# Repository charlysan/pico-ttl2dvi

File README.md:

# pico-ttl2dvi

Firmware and hardware for the RP2350 that captures **digital TTL video** from retro PC graphics cards and outputs **DVI/HDMI**, live.

TTL signals go straight into the RP2350, are sampled by PIO, 
reconstructed into a framebuffer, and re-emitted as DVI by 
[PicoDVI](https://github.com/Wren6991/PicoDVI).

> **Disclaimer.** This is an experimental hobby project. The firmware and
> hardware designs are shared as they are, with no warranty of any kind. Wiring
> a graphics card to a microcontroller means connecting 5V signals to a 3.3V
> chip, and a mistake can damage your graphics card, PC, monitor, RP2350 board
> or anything else attached. Build and use it at your own risk. The author
> accepts no responsibility for any damage or loss that results.

## Table of contents

- [Supported sources](#supported-sources)
- [Wiring](#wiring)
  - [Direct (resistors only)](#direct-resistors-only)
  - [Buffered (74HCT541 + resistors) - recommended, through-hole](#buffered-74hct541--resistors---recommended-through-hole)
  - [Buffered (74LVC245A, no resistors) - best](#buffered-74lvc245a-no-resistors---best)
  - [Controls: buttons and IR remote (optional)](#controls-buttons-and-ir-remote-optional)
- [Adapter board](#adapter-board)
- [Quick start guide](#quick-start-guide)
- [How it works](#how-it-works)
- [Modules](#modules)
- [Console](#console)
- [Tuning a card](#tuning-a-card)
- [ttl2dviPanel](#ttl2dvipanel)
- [Build](#build)
- [Hardware](#hardware)
- [Screenshots](#screenshots)
- [Discussion](#discussion)
- [Acknowledgements](#acknowledgements)
- [Licence](#licence)

## Supported sources

| Source | Data lines | Dot clock | Output |
|---|---|---|---|
| MDA / Hercules (16 MHz clone crystal) | VIDEO + INTENSITY, 2-bit | 16.000 MHz | 4-level grey |
| CGA, 640-wide modes | RGBI, 4-bit | 14.323 MHz | 16 colours |
| Commodore 128 VDC, 80-column | RGBI, 4-bit | 16.000 MHz | 16 colours |
| EGA, 350-line modes | RGBrgb, 6-bit | 17.750 MHz | 64 colours |
| EGA, 200-line modes | RGBI, 4-bit | 14.161 MHz | 16 colours |

Supports text and graphics modes. CGA and EGA 200-line modes use the standard
CGA palette (including the IBM 5153 "brown" correction). EGA switches between
its 200 and 350-line modes live, following the card.

Colour sources are encoded as RGB222, which gives about 75% of full brightness.
Turn up the monitor's brightness to compensate.

## Wiring

DE-9 from the card, 330 Ω in series on every line, into the RP2350's 5 V-tolerant
inputs.

| Signal | DE-9 | GPIO |
|---|---|---|
| VIDEO (MDA) / Secondary BLUE (EGA) | 7 | 20 |
| INTENSITY / Secondary GREEN (EGA) | 6 | 21 |
| RED | 3 | 22 |
| GREEN | 4 | 23 |
| BLUE | 5 | 24 |
| Secondary RED (EGA) | 2 | 25 |
| VSYNC | 9 | 26 |
| HSYNC | 8 | 27 |
| GND | 1 | GND |

On EGA 350-line modes, pins 2, 6 and 7 carry secondary red, green and blue. In
200-line modes the card drives it like CGA: pin 6 is INTENSITY and pins 2 and 7
are unused. Pin 2 is never ground on EGA, so use only pin 1 for GND.

DVI output pins are per board (`cmake/boards.cmake` + `src/config/board.h`);
on the default **Waveshare RP2350-PiZero** they are GPIO 32-39.

### Direct (resistors only)

The minimal hookup. The 330 Ω limits current into the RP2350 pad's clamp diode
- that diode *is* the "5 V tolerance", and the resistor is what keeps it safe.

```
   graphics card (TTL, 5V)                     RP2350
   ───────────────────────                     ──────
   DE-9 7   VIDEO      ─────[ 330Ω ]────────►  GPIO 20
   DE-9 6   INTENSITY  ─────[ 330Ω ]────────►  GPIO 21
   DE-9 3   RED        ─────[ 330Ω ]────────►  GPIO 22
   DE-9 4   GREEN      ─────[ 330Ω ]────────►  GPIO 23
   DE-9 5   BLUE       ─────[ 330Ω ]────────►  GPIO 24
   DE-9 2   sRED       ─────[ 330Ω ]────────►  GPIO 25
   DE-9 9   VSYNC      ─────[ 330Ω ]────────►  GPIO 26
   DE-9 8   HSYNC      ─────[ 330Ω ]────────►  GPIO 27
   DE-9 1   GND        ────────────────────►   GND
```

With the pad clamping, each asserted line draws a few mA from the card. Power
the Pico first, then the PC; power the PC down first.

### Buffered (74HCT541 + resistors) - recommended, through-hole

A 5 V octal buffer between card and Pico. Its CMOS inputs draw ~0 current, so
the video card's drivers are not loaded, and a fault on the Pico side cannot
reach the card. The 330 Ω moves to the buffer's *outputs*, where 5 V logic meets
the 3.3 V pad.

```
                        ┌───────── 74HCT541 ────────┐
                        │ (5V, 100nF across 19-20p) |
   DE-9 7   VIDEO  ────►│ 2  A1              Y1  18 │──[330Ω]──►  GPIO 20
   DE-9 6   INTEN  ────►│ 3  A2              Y2  17 │──[330Ω]──►  GPIO 21
   DE-9 3   RED    ────►│ 4  A3              Y3  16 │──[330Ω]──►  GPIO 22
   DE-9 4   GREEN  ────►│ 5  A4              Y4  15 │──[330Ω]──►  GPIO 23
   DE-9 5   BLUE   ────►│ 6  A5              Y5  14 │──[330Ω]──►  GPIO 24
   DE-9 9   VSYNC  ────►│ 7  A6              Y6  13 │──[330Ω]──►  GPIO 26
   DE-9 8   HSYNC  ────►│ 8  A7              Y7  12 │──[330Ω]──►  GPIO 27
   DE-9 2   sRED   ────►│ 9  A8              Y8  11 │──[330Ω]──►  GPIO 25
                        │                           │
                 GND ──►│ 1  /OE1          /OE2  19 │◄── GND
                 GND ──►│ 10 GND            Vcc  20 │◄── +5V
                        └───────────────────────────┘

   DE-9 1   GND ─────────────── common ground ──────────────►  GND
```

Both `/OE` pins (1 and 19) must go to GND, and keep one common ground between
card, buffer and Pico.

Use the **HCT** part, not plain HC: its TTL-level input thresholds read a 5 V
TTL high reliably at 5 V Vcc.

### Buffered (74LVC245A, no resistors) - best

The same idea, but powered at **3.3 V**. LVC inputs accept 5.5 V regardless of
Vcc - 5 V tolerance is a designed-in property of the family, so the card connects 
straight in and the outputs are already 3.3 V logic.

```
                    ┌───────── 74LVC245A ─────────┐
                    │ (3.3V, 100nF across 10-20p) │
   DE-9 7  VIDEO ──►│ 2  A1                B1  18 │────►  GPIO 20
   DE-9 6  INTEN ──►│ 3  A2                B2  17 │────►  GPIO 21
   DE-9 3  RED   ──►│ 4  A3                B3  16 │────►  GPIO 22
   DE-9 4  GREEN ──►│ 5  A4                B4  15 │────►  GPIO 23
   DE-9 5  BLUE  ──►│ 6  A5                B5  14 │────►  GPIO 24
   DE-9 9  VSYNC ──►│ 7  A6                B6  13 │────►  GPIO 26
   DE-9 8  HSYNC ──►│ 8  A7                B7  12 │────►  GPIO 27
   DE-9 2  sRED  ──►│ 9  A8                B8  11 │────►  GPIO 25
                    │                             │
            +3V3 ──►│ 1  DIR                      │  DIR high = A→B
             GND ──►│ 19 /OE              Vcc  20 │◄── +3V3 (Pico 3V3 pin)
                    │ 10 GND                      │
                    └─────────────────────────────┘

   DE-9 1  GND ─────────────── common ground ──────────────►  GND
```

`DIR` high and `/OE` low enable the A→B direction; both must be tied, not left
floating. Power it from the Pico's **3V3** pin - the 5 V tolerance depends on
Vcc being 3.3 V.

Beyond dropping the resistors, this also removes the power-sequencing rule: LVC
supports partial power-down, so the card may be live while the Pico is off.

### Controls: buttons and IR remote (optional)

Three push buttons and an IR receiver drive a one-line on-screen menu, so the
box can be tuned without a computer. Both are optional.

| Function | GPIO | Header pin (Pi layout) |
|---|---|---|
| IR receiver output | 6 | 31 |
| Button PREV (previous / -1) | 7 | 26 |
| Button NEXT (next / +1) | 8 | 24 |
| Button ENTER (short: select, long: back) | 9 | 21 |

Hold **ENTER + PREV** for 2 s to reset, **ENTER + NEXT** for 2 s to reboot into
USB BOOTSEL (for a UF2). The screen counts down; let go to cancel.

```
   push buttons (each one to GND)              RP2350
   ──────────────────────────────              ──────
          ┌─── PREV ───┐
   GND ───┤            ├───────────────────►  GPIO 7
          └─── o  o ───┘
          ┌─── NEXT ───┐
   GND ───┤            ├───────────────────►  GPIO 8
          └─── o  o ───┘
          ┌── ENTER ───┐
   GND ───┤            ├───────────────────►  GPIO 9
          └─── o  o ───┘

   IR receiver (KY-022 / VS1838B)
   ──────────────────────────────
          ┌───────────┐
          │  KY-022   │
          │         S ├─────────────────────►  GPIO 6
          │       VCC ├──────┬──────────────◄  3V3
          │           │     ═╪═ 100nF 
          │         - ├──────┴───────────────  GND
          └───────────┘
```

- **No resistors.** The firmware enables the internal pull-ups, so a button
  reads low while pressed. Wire buttons to **GND**, not to 3V3 with
  pull-downs: RP2350 erratum E9 can latch an input with the internal pull-down
  at ~2 V.
- **Power the IR receiver from 3V3**, not 5 V: its output is pulled up to its
  own supply, so at 3V3 it connects straight to the GPIO.
- **Put a 100 nF capacitor across the receiver's VCC and GND**, right at the
  module. Without it, the switching noise from the video inputs reaches the
  receiver through its supply, and its LED flickers 
  (observed when switching to EGA 350-line (1 px stripes or checkerboards).
- The remote must speak **NEC**, which most cheap remotes do.

To use a remote, either:

- **on the box:** Menu → Remote → Learn, then follow the on-screen prompts
  with the push buttons. It asks for the navigation keys, then offers
  shortcuts from a list (OSD status/live/hide, scanlines, load slot 0-7); or
- **from a computer:** record its buttons with `tools/irlearn.py --learn
  ir.txt`, turn the map into a UF2 with `tools/irmap2uf2.py ir.txt`, and drop
  `irmap.uf2` on the BOOTSEL drive (or `picotool load -f irmap.uf2`). This
  route can put any console command on a key.

Firmware updates leave the map in place.

## Adapter board

An experimental through-hole board design (KiCad) is in [hardware/tht](./hardware/tht/). See the [hardware documentation](./hardware/README.md) for how to build one.
Rev A is untested; only the breadboard prototype has been verified.

## Quick start guide

You can check the Quick Start Guide documentation [here](./docs/quickstart.md)

## How it works

```
  TTL video ──> [capture] ──> rawbuf ──> [view] ──> framebuffer ──> [video] ──> DVI
                pio0/core0                core0                   pio1/core1
                   ^
                   |
                [sync] ──> [sigcheck] ──> [detect] ──> reboot into another source
             HSYNC/VSYNC   rate check    auto source
             measurement
```

**No CPU sits in any per-line timing path.** PIO waits on sync edges; 
the CPU only acts once per frame, during vertical blanking. Capture and
DVI are on separate PIOs and separate cores, so neither can stall the other.

Core 0 only does the per-frame work: it waits for the VSYNC edge, sizes the
sampling window from the sync measurement, arms the DMA and the sampler, and
when the frame ends reconstructs it with `view`. Per line, the PIO locks to each
HSYNC edge and DMA stores the samples, with no CPU involved.

The source (card descriptor) configures both sides at boot: capture gets the
data pins, dot clock and default `bp`/`phase`; video gets the DVI raster and
encoder.

Per frame:

1. **`sync`** measures the HSYNC period and pulse width with a PIO countdown.
2. **`capture`** sizes its sampling window from that measurement, then a single
   DMA transfer records one VSYNC-bounded frame of raw samples into `rawbuf`.
   Sampling is 1x or 2x, picked per source: 2x when the dot clock is not close
   enough to a whole number of system clocks, so reconstruction can pick the
   sample nearest each pixel's centre rather than its edge.
3. **`view`** reconstructs each line, maps sample values to grey levels or
   RGB222 colours, and writes the result into the framebuffer at the current
   position (`hpos`/`vpos`).
4. **`video`** on core 1 walks the framebuffer, repeats rows for vertical scale,
   adds the letterbox, TMDS-encodes each scanline and feeds the serialiser
   continuously.

**Signal check and auto source.** `sigcheck` checks the HSYNC/VSYNC rates
against known ranges. Once they are stable, `detect` picks the source from the
line rate, and from the measured dot clock when several sources share a line
rate. If it finds a different card, it reboots into that source.

## Modules

| Path | Role |
|---|---|
| `src/config` | Board pins and DVI pin config; the source-card descriptors (pins, dot clock, sysclk, defaults) |
| `src/capture` | PIO sampler + DMA into `rawbuf`; per-line reconstruction; signal check. `capture.pio`, `sync_period.pio` |
| `src/video` | Framebuffer, DVI raster tables, TMDS encoding on core 1, colour tables |
| `src/view` | Scan converter: joins capture and video, owns all display framing |
| `src/settings` | Persistent settings slots in the last flash sector |
| `src/console` | USB CDC command console |
| `apps/ttl2dvi` | The application: startup order + command table (`main.c`), command bodies (`commands.c`), source detection (`detect.c`), OSD messages (`osd.c`), buttons and menu (`buttons.c`, `menu.c`), IR remote and learning (`remote.c`, `learn.c`), auto tune (`tune.c`) |
| `src/ir` | NEC IR decoder on pio2 |
| `apps/dvi_test` | Standalone DVI test card, links libdvi only |
| `extern/dvi` | Vendored PicoDVI (`libdvi`) (fork from [mlorenzati](https://github.com/mlorenzati/PicoDVI)) |
| `tools` | `ttl2dviPanel.py` control panel, `grab.py` frame grabber, `autotune.py` dot clock and phase tuning, `irlearn.py` / `irmap2uf2.py` IR key maps |

Everything that differs between cards - data pins, dot clock, system clock,
framebuffer depth, TMDS encoder, DVI raster - is selected from the source
descriptor at boot. Switching card reboots into the new configuration.

## Console

Connect to the USB serial port (115200 baud, any terminal) and type `help`.

```
source [n]           select the card (reboots)
source auto on|off   automatic source detection (stored in flash)
mode [n]             DVI output raster (reboots)
status / state       signal and settings; state prints one line for tools
bp / phase           capture framing: sampling window, sub-pixel sampling instant
dotclock [MHz]       card dot clock, or default
hpos / vpos          display position
vscale [1..4]        vertical scale
scanlines on|off|switch  blank every other line (vscale >= 2)
mdalevels            MDA grey levels
slots                saved settings for this source
save / load / clear  settings slots in flash (8 per source)
default [n|off]      slot applied at boot
detect / measure     which source auto would pick / measure the dot clock
tune [apply]         measure the dot clock and pick the phase (auto tune)
osd ...              on-screen display; osd live toggles live measurements
ir on|off / ir map   print IR remote codes / list the loaded key map
reboot / bootsel     reboot / reboot into USB BOOTSEL (for a UF2)
capture / fastcap    dump a frame over USB (tools/grab.py, tools/autotune.py)
dvi_test             on-screen test pattern
```

Example:
```
screen /dev/tty.usbmodem1101 115200

ttl2dvi> source
  auto detection: on
  0  MDA16  2 data bits @ GP20, 720 px, 16.000 MHz dot, sysclk 256 MHz   <- current
  1  CGA    4 data bits @ GP21, 640 px, 14.322 MHz dot, sysclk 258 MHz
  2  C128   4 data bits @ GP21, 640 px, 16.000 MHz dot, sysclk 256 MHz
  3  EGA    6 data bits @ GP20, 640 px, 17.750 MHz dot, sysclk 266.4 MHz, both families
ttl2dvi> source 1
switching to CGA...
```

## Tuning a card

If a card's crystal differs from the defaults, the picture shimmers or shows
evenly spaced vertical bars. Put text or a test pattern on screen, then:

- **on the box:** Menu → Sampling → Auto tune. It measures the dot clock from
  pixel edges, picks the phase, shows the result, and offers Apply, Apply and
  save to a slot, or Cancel;
- **on the console:** `tune` prints the same result, `tune apply` applies it;
- **from a computer:** `tools/autotune.py` does the same from a `fastcap`
  dump, with an edge histogram and the best phases listed.

Auto tune and `tune` search from -25% to +33% of the current dot clock, so a
card on a different crystal is usually found without changing the source.
If the result isn't a whole fraction of the system clock it says "may
shimmer": it works, but a source built for that clock would be cleaner.
`autotune.py` searches ±5%; for it, set `dotclock` near the card's first.
`bp` (the left edge) is not tuned. Save the result in a slot.

## ttl2dviPanel

`tools/ttl2dviPanel.py` is a Tk GUI over the same console
(`pip install -r tools/requirements.txt`). It polls `state` once a second, so
the knobs follow changes made from the console.

## Build

Requires the Pico SDK (2.3+) and CMake:

```sh
mkdir build && cd build
cmake -DTTL_BOARD=pizero ..
make -j
```

Or you can use [Docker](https://github.com/lukstep/raspberry-pi-pico-docker-sdk):

```sh
 docker run -d -it --name pico-sdk \
 --mount type=bind,source=${PWD},target=/home/dev \
 lukstep/raspberry-pi-pico-sdk:v1.2.0
 ```

```sh
docker exec -it pico-sdk sh -c \
"cd /home/dev/build && cmake \
-DTTL_BOARD=pizero \
-DPICO_PLATFORM=rp2350-arm-s .. \
&& make -j\$(nproc)"
```

`TTL_BOARD` selects the hardware profile (`pizero` | `pico2_dvi`) and is the
single source of truth for the board. The output is `build/apps/ttl2dvi/ttl2dvi.uf2`.

Then just upload the .uf2 file to rp2350 (in BOOTSEL mode). For example:
```sh
cp build/apps/ttl2dvi/ttl2dvi.uf2 /Volumes/RP2350
```

## Hardware

Tested on a [Waveshare RP2350-PiZero](https://www.waveshare.com/wiki/RP2350-PiZero) (RP2350B, 48 GPIO, 520 KB SRAM).

## Screenshots

Check [Wiki](https://github.com/charlysan/pico-ttl2dvi/wiki/Pico-TTL2DVI-Intro) for some screenshots.

## Discussion

- [VCFed](https://forum.vcfed.org/index.php?threads/pico-ttl2dvi-convert-ttl-video-to-hdmi.1258490/)

## Acknowledgements

Inspired by [mlorenzati/pico-rgb2hdmi](https://github.com/mlorenzati/pico-rgb2hdmi), which
converts analog RGB to HDMI on an RP2040. 

DVI output is [PicoDVI](https://github.com/Wren6991/PicoDVI) by Luke Wren.

## Licence

MIT.

`extern/dvi` is vendored PicoDVI and keeps its own licence - see
`extern/dvi/LICENSE`.

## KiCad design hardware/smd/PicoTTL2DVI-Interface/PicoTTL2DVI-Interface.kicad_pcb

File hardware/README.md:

# Hardware

Through-hole adapter board for the [Waveshare RP2350-PiZero](https://www.waveshare.com/wiki/RP2350-PiZero).
It takes the graphics card's TTL video on a DE-9 (or an IDC10 header), buffers it,
and feeds it to the RP2350. The HDMI output is the Waveshare's own mini HDMI.

> **Disclaimer.** Experimental hobby hardware, shared as it is, with no
> warranty. See the [main README](../README.md).

> **Not tested yet.** The rev A board has not been built (yet). The circuit was
> tested on a breadboard prototype (74HCT541 + 330 Ω), not on this PCB.

## Files

Everything for a revision is under `tht/rev<X>/`. For rev A:

| File | What |
|---|---|
| [`gerbers/ttl2dvi_tht_revA.zip`](./tht/revA/gerbers/ttl2dvi_tht_revA.zip) | Gerbers + drill files, ready to upload |
| [`BOM.txt`](./tht/revA/BOM.txt) | Bill of materials, with an "optional" column |
| [`schematic/schematic_tht_reva.pdf`](./tht/revA/schematic/schematic_tht_reva.pdf) | Schematic |
| `ttl2dvi_tht.kicad_*` | KiCad 10 project |

## Ordering the PCB

Upload the gerber `.zip` file as is to your PCB manufacturer (I've used JLCPCB constraints).
`THT` means that every part is through hole, so no assembly service is needed.

## HCT or LVC

U1 (buffer) and U2 (Schmitt) are socketed, and the board takes either logic
family. Pick one family for both chips.

| Build | U1 | U2 | Supply | Notes |
|---|---|---|---|---|
| **HCT** | 74HCT541 | 74HCT14 | 5 V | Keeps the power-sequencing rule (below). |
| **LVC** | 74LVC245A | 74LVC14A | 3.3 V | No power-sequencing rule. |

Both should work. However, I have only tested with HCT. LVC is the better choice if you can
get it though.

**HCT only: power the Pico first, then the PC. Turn the PC off first, then the
Pico.** With LVC the card may be live while the Pico is off.

R1-R8 (330 Ω) are fitted in both builds.

## Jumpers

All four are 1x3 headers. So, you can use a shunt or just solder a jumper.

| Jumper | Sets | 1-2 | 2-3 |
|---|---|---|---|
| JP1 | buffer supply | 3V3 (**LVC**) | 5V (**HCT**) |
| JP2 | U1 pin 1 | DIR, '245 (**LVC**) | /OE1, '541 (**HCT**) |
| JP3 | HSYNC source | U1 buffer | U2 Schmitt |
| JP4 | VSYNC source | U1 buffer | U2 Schmitt |

- JP1 and JP2 always go together: both on LVC, or both on HCT.
- **No U2 fitted: JP3 and JP4 on 1-2.** On 2-3 the syncs come from an empty
  socket and nothing is captured.

## What to populate

You do not need to fit everything. The minimum is:

- J1 (2x20 female header) and the Waveshare module
- J2 (DE-9) **or** J3 (IDC10)
- U1 + socket, C1, C2
- R1-R8
- JP1-JP4 + shunts

The rest is optional. Check the "optional" column in [`BOM.txt`](./tht/revA/BOM.txt).

| Part | What for |
|---|---|
| J3 | Alternative input: a DE9-to-IDC10 cable (IDC pin n = DE-9 pin n). **Use one input only**, never J2 and J3 at once |
| U2 + socket | Schmitt trigger on HSYNC/VSYNC. Not needed so far; added for experimentation when HSYNC is distorted / degraded. |
| SW1-SW3 | PREV / NEXT / ENTER buttons for the on-screen menu  (OSD)|
| U3, R9, C4 | IR receiver for a remote. R9 and C4 are required when U3 is fitted |
| D1, R10 | IR activity LED, for debugging |
| J4 | Logic analyser header (GPIO 20-27 + GND) |
| J5, R11, R12 | Serial console pins. R11/R12 sit under the module. |
| J6, D2 | External 5 V input |

## Mounting the Waveshare

The module plugs in **face down**: component side towards the adapter board,
with its USB-C and mini HDMI at the board edge. Its BOOT and RUN buttons are
not reachable that way. Use `picotool reboot -f -u`, the `bootsel` console
command, or hold **ENTER + NEXT** for 2 s to get into BOOTSEL.

## Power

Power the board from **either** the Waveshare's USB-C **or** J6 (5V IN).

> **NEVER connect J6 and a USB-C cable at the same time.** The 5 V pins on
> the header are the Waveshare's USB VBUS. D2 stops USB from feeding the
> external supply, but not the other way round!

Never feed anything into a 3V3 pin.

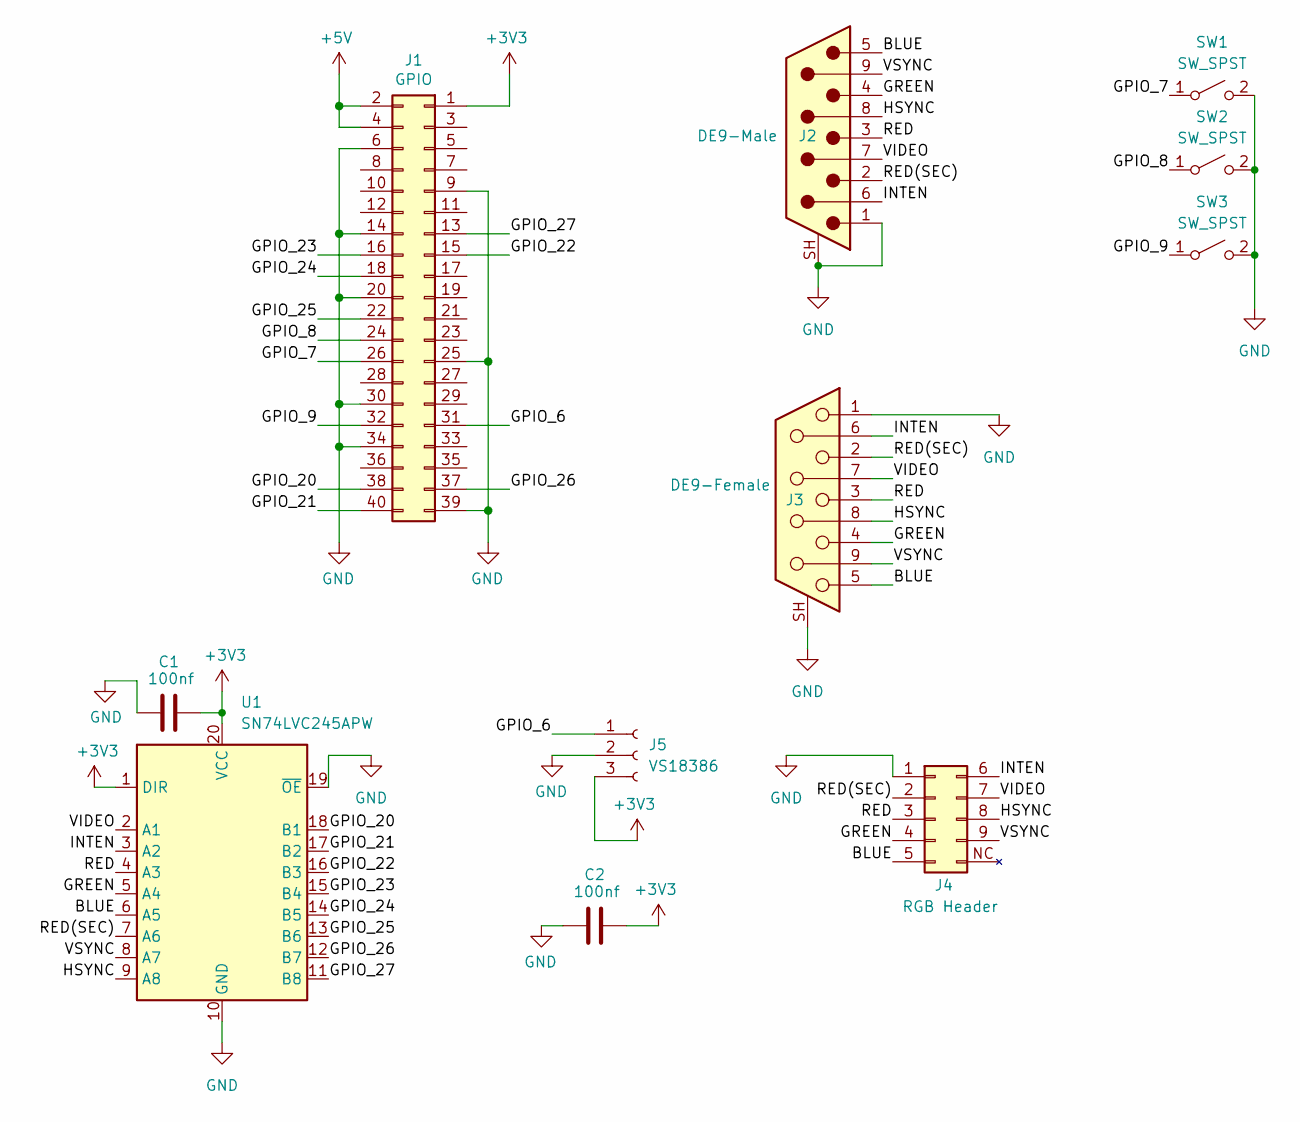
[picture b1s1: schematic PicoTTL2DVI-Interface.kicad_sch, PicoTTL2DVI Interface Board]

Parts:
C1, C2: 100nf; C_0805_2012Metric_Pad1.18x1.45mm_HandSolder
J1: GPIO; PinSocket_2x20_P2.54mm_Vertical
J2: DE9-Male; DSUB-9_Pins_EdgeMount_P2.77mm
J3: DE9-Female; DSUB-9_Socket_EdgeMount_P2.77mm
J4: RGB Header; PinHeader_2x05_P2.54mm_Vertical
J5: VS18386; PinHeader_1x03_P2.54mm_Vertical
SW1, SW2, SW3: SW_SPST; SW_PUSH_6mm
U1: SN74LVC245APW; TSSOP-20_4.4x6.5mm_P0.65mm

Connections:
+3V3: C1.2, C2.2, J1.1, J5.3, U1.1 (DIR), U1.20 (VCC)
+5V: J1.2, J1.4
/BLUE: J2.5, J3.5, J4.5, U1.6 (A5)
/GPIO_6: J1.31, J5.1
/GPIO_7: J1.26, SW1.1 (A)
/GPIO_8: J1.24, SW2.1 (A)
/GPIO_9: J1.32, SW3.1 (A)
/GPIO_20: J1.38, U1.18 (B1)
/GPIO_21: J1.40, U1.17 (B2)
/GPIO_22: J1.15, U1.16 (B3)
/GPIO_23: J1.16, U1.15 (B4)
/GPIO_24: J1.18, U1.14 (B5)
/GPIO_25: J1.22, U1.13 (B6)
/GPIO_26: J1.37, U1.12 (B7)
/GPIO_27: J1.13, U1.11 (B8)
/GREEN: J2.4, J3.4, J4.4, U1.5 (A4)
/HSYNC: J2.8, J3.8, J4.8, U1.9 (A8)
/INTEN: J2.6, J3.6, J4.6, U1.3 (A2)
/RED: J2.3, J3.3, J4.3, U1.4 (A3)
/RED(SEC): J2.2, J3.2, J4.2, U1.7 (A6)
/VIDEO: J2.7, J3.7, J4.7, U1.2 (A1)
/VSYNC: J2.9, J3.9, J4.9, U1.8 (A7)
GND: C1.1, C2.1, J1.6, J1.9, J1.14, J1.20, J1.25, J1.30, J1.34, J1.39, J2.1, J2.SH (PAD), J3.1, J3.SH (PAD), J4.1, J5.2, SW1.2 (B), SW2.2 (B), SW3.2 (B), U1.10 (GND), U1.19 (~OE)

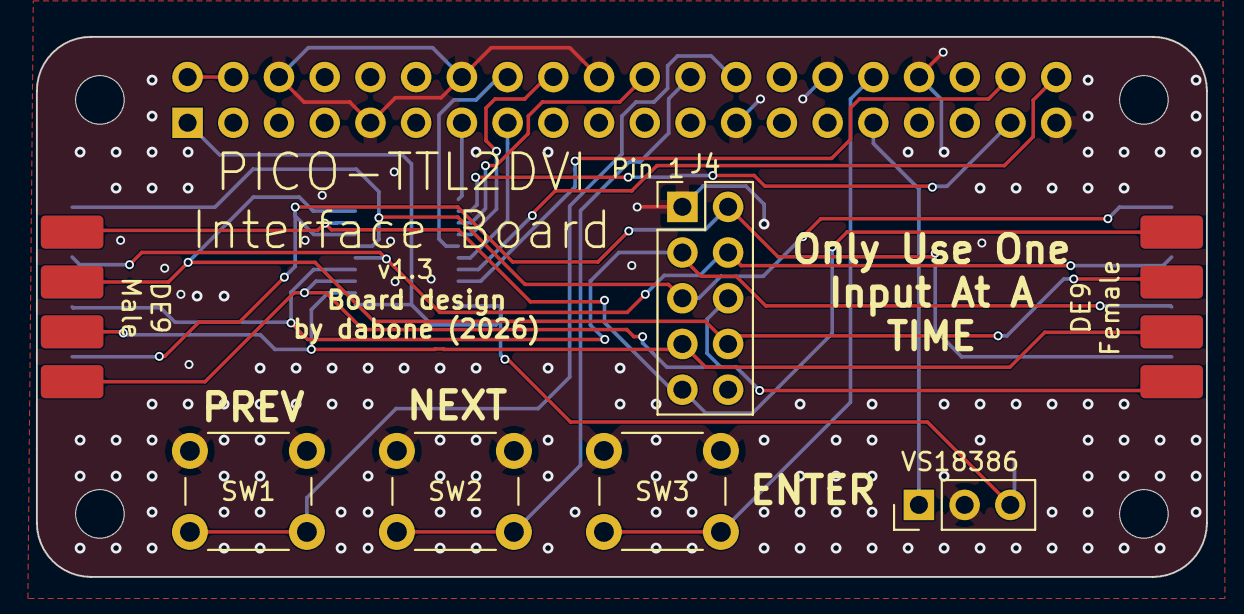
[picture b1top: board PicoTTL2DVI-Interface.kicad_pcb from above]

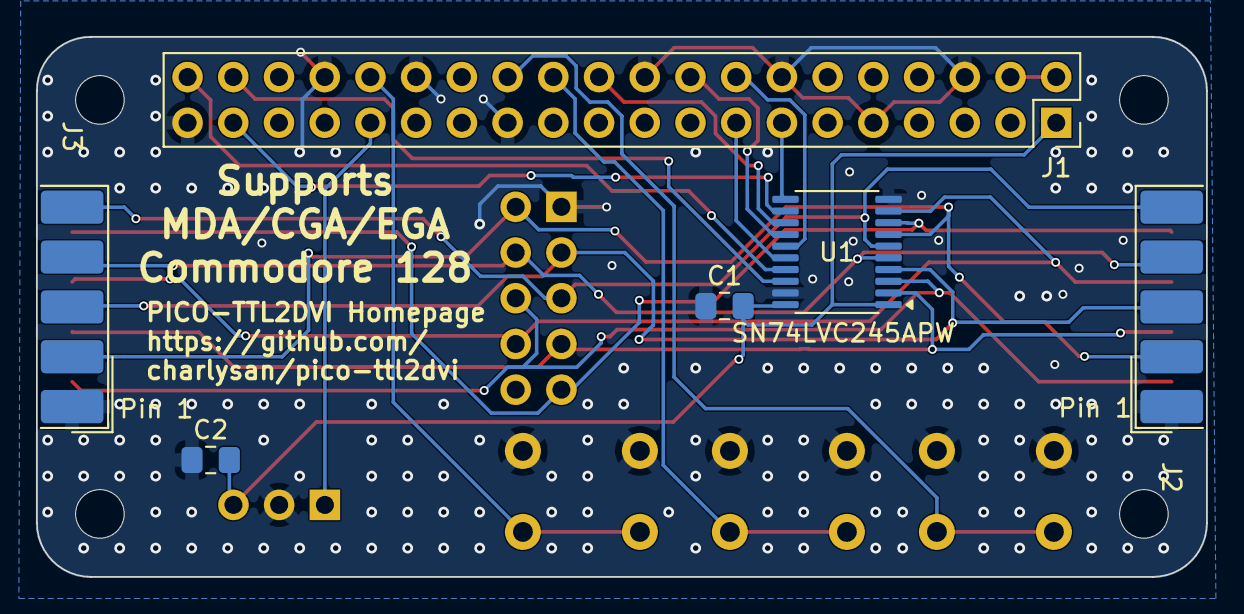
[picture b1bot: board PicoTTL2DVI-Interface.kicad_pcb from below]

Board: 2 copper layers, 65.0 x 30.0 mm, 15 parts (6 on the bottom side), 23 nets.

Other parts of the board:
MH1, MH2, MH3, MH4: MountingHole_2.7mm_M2.5

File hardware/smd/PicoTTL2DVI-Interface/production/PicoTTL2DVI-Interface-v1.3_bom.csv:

Designator,Footprint,Quantity,Value,LCSC Part #
"C1, C2",0805,2,100nf,
J1,PinSocket_2x20_P2.54mm_Vertical,1,GPIO,
J2,DSUB-9_Pins_EdgeMount_P2.77mm,1,DE9-Male,
J3,DSUB-9_Socket_EdgeMount_P2.77mm,1,DE9-Female,
J4,PinHeader_2x05_P2.54mm_Vertical,1,RGB Header,
J5,PinHeader_1x03_P2.54mm_Vertical,1,VS18386,
"SW1, SW2, SW3",SW_PUSH_6mm,3,SW_SPST,
U1,TSSOP-20_4.4x6.5mm_P0.65mm,1,SN74LVC245APW,

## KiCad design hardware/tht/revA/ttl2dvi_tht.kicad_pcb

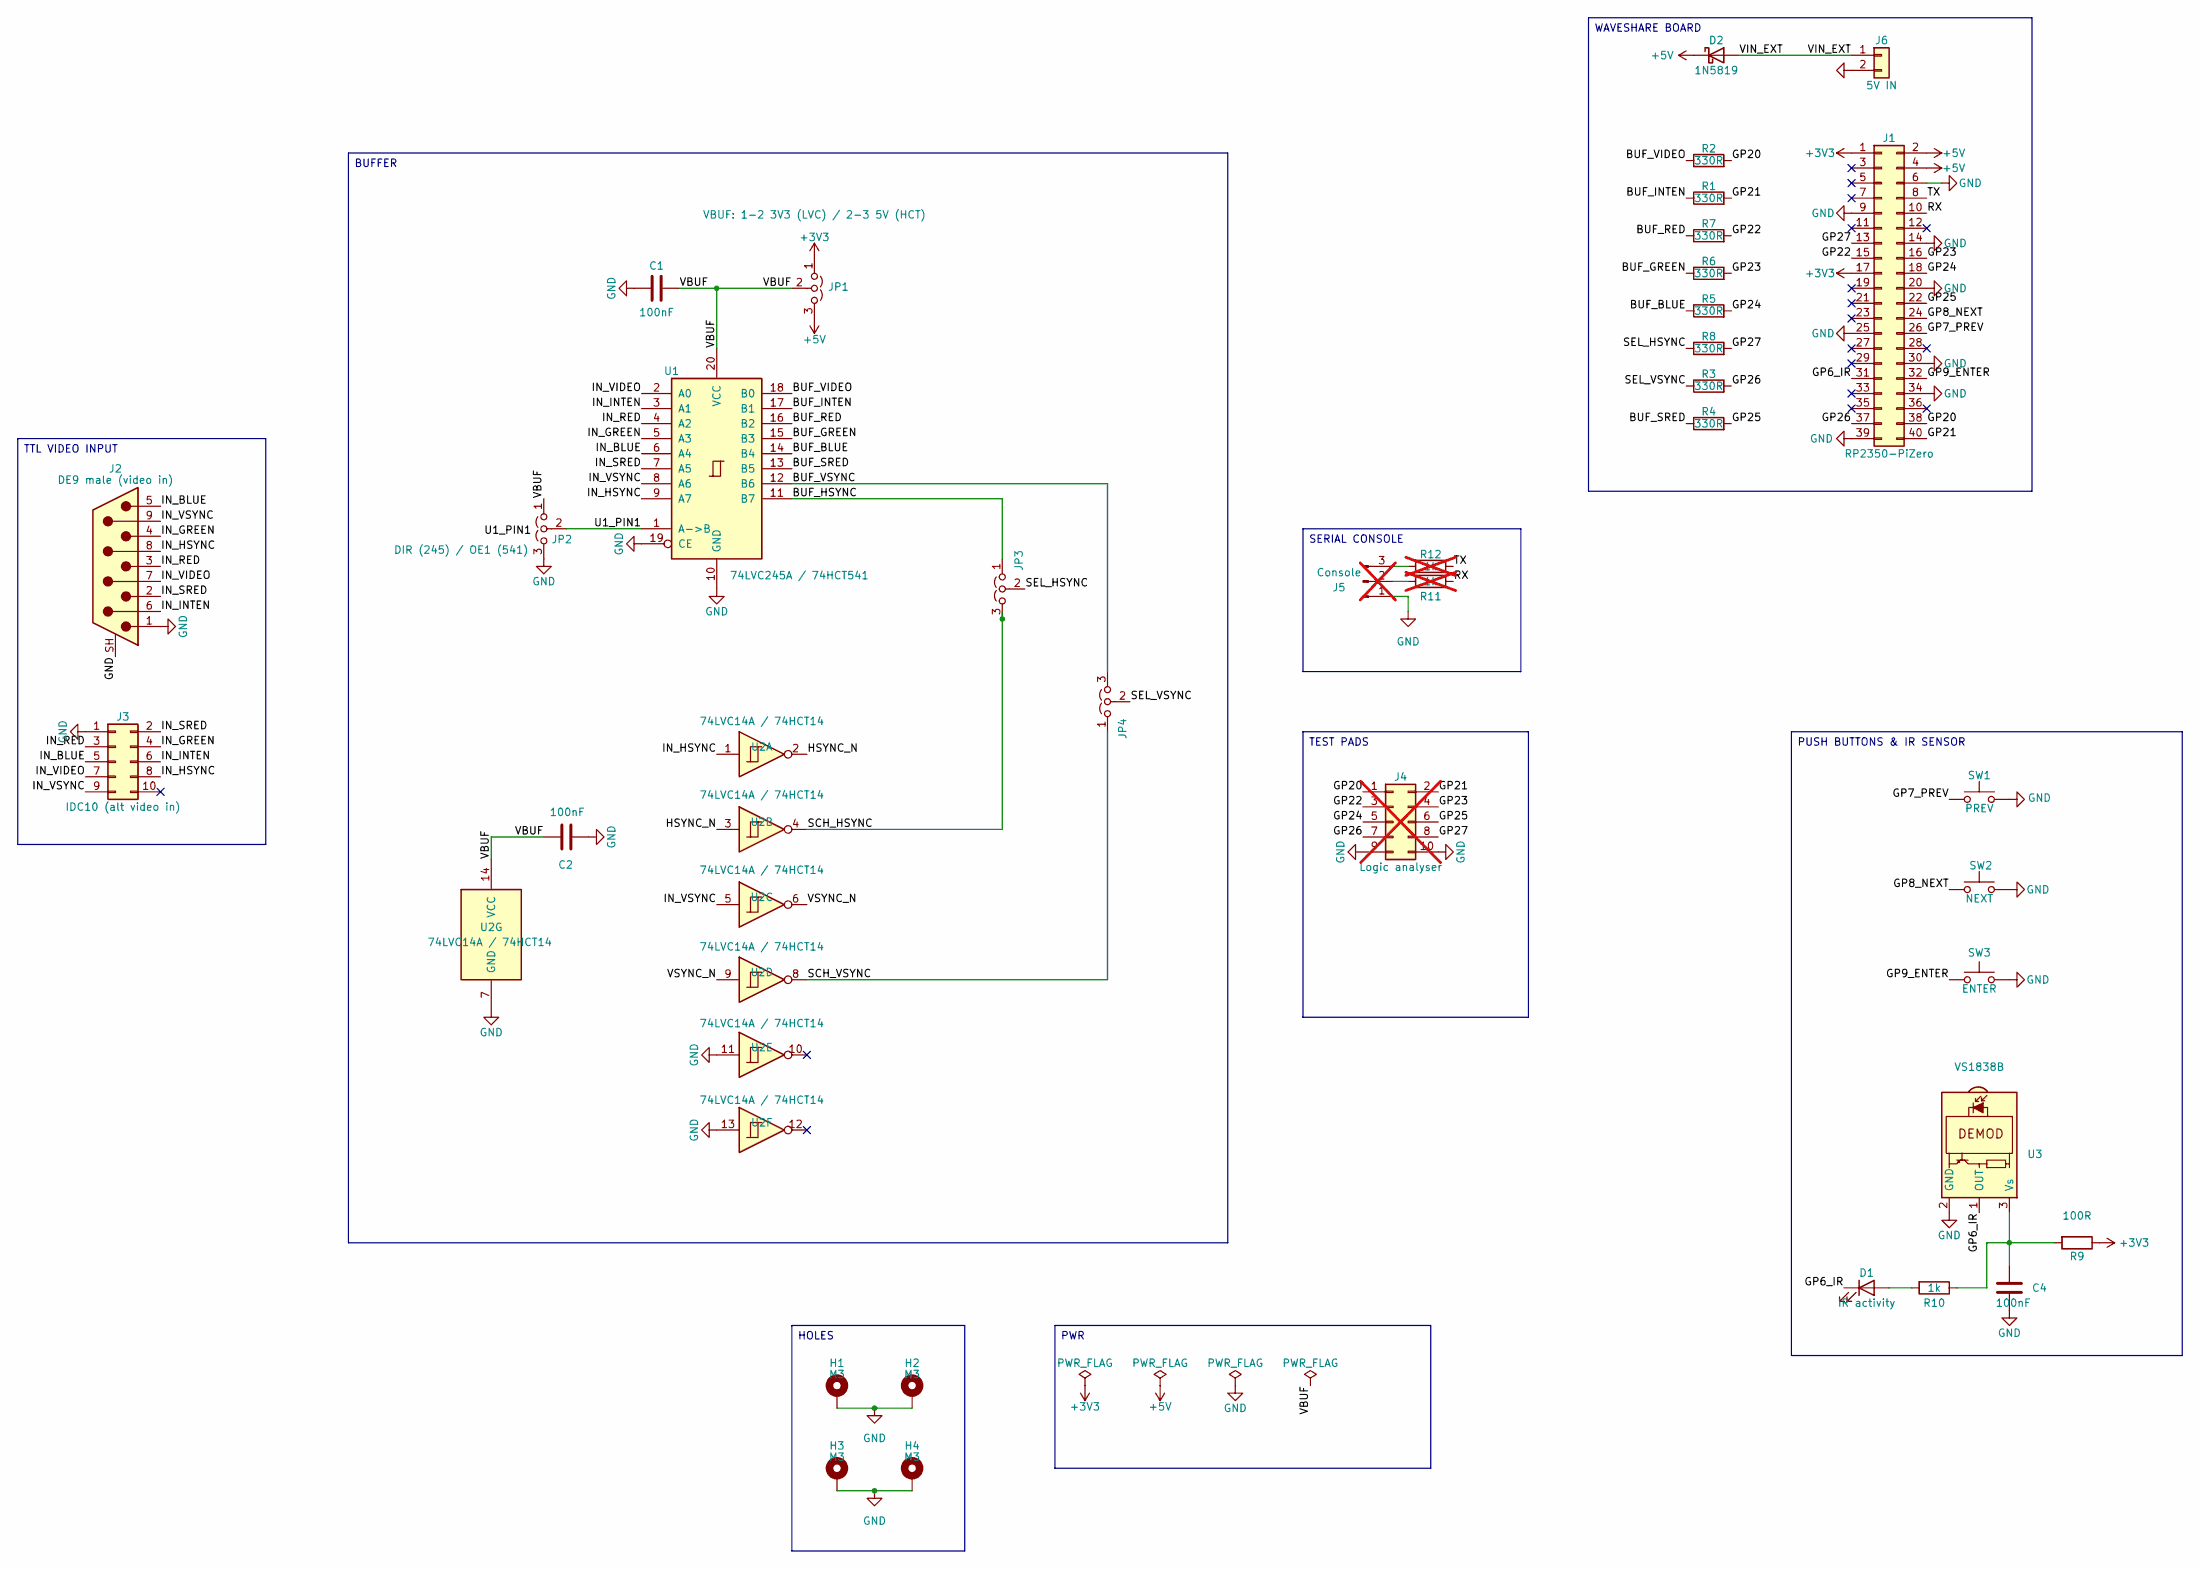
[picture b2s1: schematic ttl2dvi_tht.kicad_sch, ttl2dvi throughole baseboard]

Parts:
C1, C2, C4: 100nF; C_Disc_D5.0mm_W2.5mm_P5.00mm
D1: IR activity; LED_D3.0mm
D2: 1N5819; D_DO-41_SOD81_P10.16mm_Horizontal
H1, H2, H3, H4: M3; MountingHole_3.2mm_M3_Pad_Via
J1: RP2350-PiZero; Raspberry_Pi_Zero_Socketed_THT_FaceDown_MountingHoles
J2: DE9 male (video in); DSUB-9_Pins_Horizontal_P2.77x2.84mm_EdgePinOffset7.70mm_Hou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
J3: IDC10 (alt video in); IDC-Header_2x05_P2.54mm_Vertical
J4: Logic analyser; PinHeader_2x05_P2.54mm_Vertical; not fitted
J5: Console; PinHeader_1x03_P2.54mm_Vertical; not fitted
J6: 5V IN; JST_XH_B2B-XH-A_1x02_P2.50mm_Vertical
JP1: VBUF: 1-2 3V3 (LVC) / 2-3 5V (HCT); PinHeader_1x03_P2.54mm_Vertical
JP2: DIR (245) / OE1 (541); PinHeader_1x03_P2.54mm_Vertical
JP3: HSYNC: 1-2 BUF / 2-3 SCH; PinHeader_1x03_P2.54mm_Vertical
JP4: VSYNC: 1-2 BUF / 2-3 SCH; PinHeader_1x03_P2.54mm_Vertical
R1, R2, R3, R4, R5, R6, R7, R8: 330R; R_Axial_DIN0207_L6.3mm_D2.5mm_P7.62mm_Horizontal
R9: 100R; R_Axial_DIN0207_L6.3mm_D2.5mm_P7.62mm_Horizontal
R10: 1k; R_Axial_DIN0207_L6.3mm_D2.5mm_P7.62mm_Horizontal
R11, R12: 1k; R_Axial_DIN0207_L6.3mm_D2.5mm_P7.62mm_Horizontal; not fitted
SW1: PREV; SW_PUSH_6mm
SW2: NEXT; SW_PUSH_6mm
SW3: ENTER; SW_PUSH_6mm
U1: 74LVC245A / 74HCT541; DIP-20_W7.62mm_Socket
U2: 74LVC14A / 74HCT14; DIP-14_W7.62mm_Socket
U3: VS1838B; Vishay_MOLD-3Pin

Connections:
+3V3: J1.1, J1.17, JP1.1 (A), R9.1
+5V: D2.1 (K), J1.2, J1.4, JP1.3 (B)
/BUF_BLUE: R5.1, U1.14 (B4)
/BUF_GREEN: R6.1, U1.15 (B3)
/BUF_HSYNC: JP3.1 (A), U1.11 (B7)
/BUF_INTEN: R1.1, U1.17 (B1)
/BUF_RED: R7.1, U1.16 (B2)
/BUF_SRED: R4.1, U1.13 (B5)
/BUF_VIDEO: R2.1, U1.18 (B0)
/BUF_VSYNC: JP4.3 (B), U1.12 (B6)
/GP6_IR: D1.1 (K), J1.31, U3.1 (OUT)
/GP7_PREV: J1.26, SW1.1
/GP8_NEXT: J1.24, SW2.1
/GP9_ENTER: J1.32, SW3.1
/GP20: J1.38, J4.1, R2.2
/GP21: J1.40, J4.2, R1.2
/GP22: J1.15, J4.3, R7.2
/GP23: J1.16, J4.4, R6.2
/GP24: J1.18, J4.5, R5.2
/GP25: J1.22, J4.6, R4.2
/GP26: J1.37, J4.7, R3.2
/GP27: J1.13, J4.8, R8.2
/HSYNC_N: U2.2, U2.3
/IN_BLUE: J2.5, J3.5, U1.6 (A4)
/IN_GREEN: J2.4, J3.4, U1.5 (A3)
/IN_HSYNC: J2.8, J3.8, U1.9 (A7), U2.1
/IN_INTEN: J2.6, J3.6, U1.3 (A1)
/IN_RED: J2.3, J3.3, U1.4 (A2)
/IN_SRED: J2.2, J3.2, U1.7 (A5)
/IN_VIDEO: J2.7, J3.7, U1.2 (A0)
/IN_VSYNC: J2.9, J3.9, U1.8 (A6), U2.5
/RX: J1.10, R11.1
/SCH_HSYNC: JP3.3 (B), U2.4
/SCH_VSYNC: JP4.1 (A), U2.8
/SEL_HSYNC: JP3.2 (C), R8.1
/SEL_VSYNC: JP4.2 (C), R3.1
/TX: J1.8, R12.1
/U1_PIN1: JP2.2 (C), U1.1 (A->B)
/VBUF: C1.2, C2.1, JP1.2 (C), JP2.1 (A), U1.20 (VCC), U2.14 (VCC)
/VIN_EXT: D2.2 (A), J6.1
/VSYNC_N: U2.6, U2.9
GND: C1.1, C2.2, C4.2, H1.1 (1_1), H2.1 (1_1), H3.1 (1_1), H4.1 (1_1), J1.6, J1.9, J1.14, J1.20, J1.25, J1.30, J1.34, J1.39, J2.1, J2.SH (PAD), J3.1, J4.9, J4.10, J5.1, J6.2, JP2.3 (B), SW1.2, SW2.2, SW3.2, U1.10 (GND), U1.19 (CE), U2.7 (GND), U2.11, U2.13, U3.2 (GND)
unnamed: D1.2 (A), R10.2
unnamed: J5.2, R11.2
unnamed: J5.3, R12.2
unnamed: C4.1, R9.2, R10.1, U3.3 (Vs)

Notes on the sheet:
WAVESHARE BOARD
PUSH BUTTONS & IR SENSOR
TEST PADS
BUFFER
SERIAL CONSOLE
TTL VIDEO INPUT
HOLES
PWR

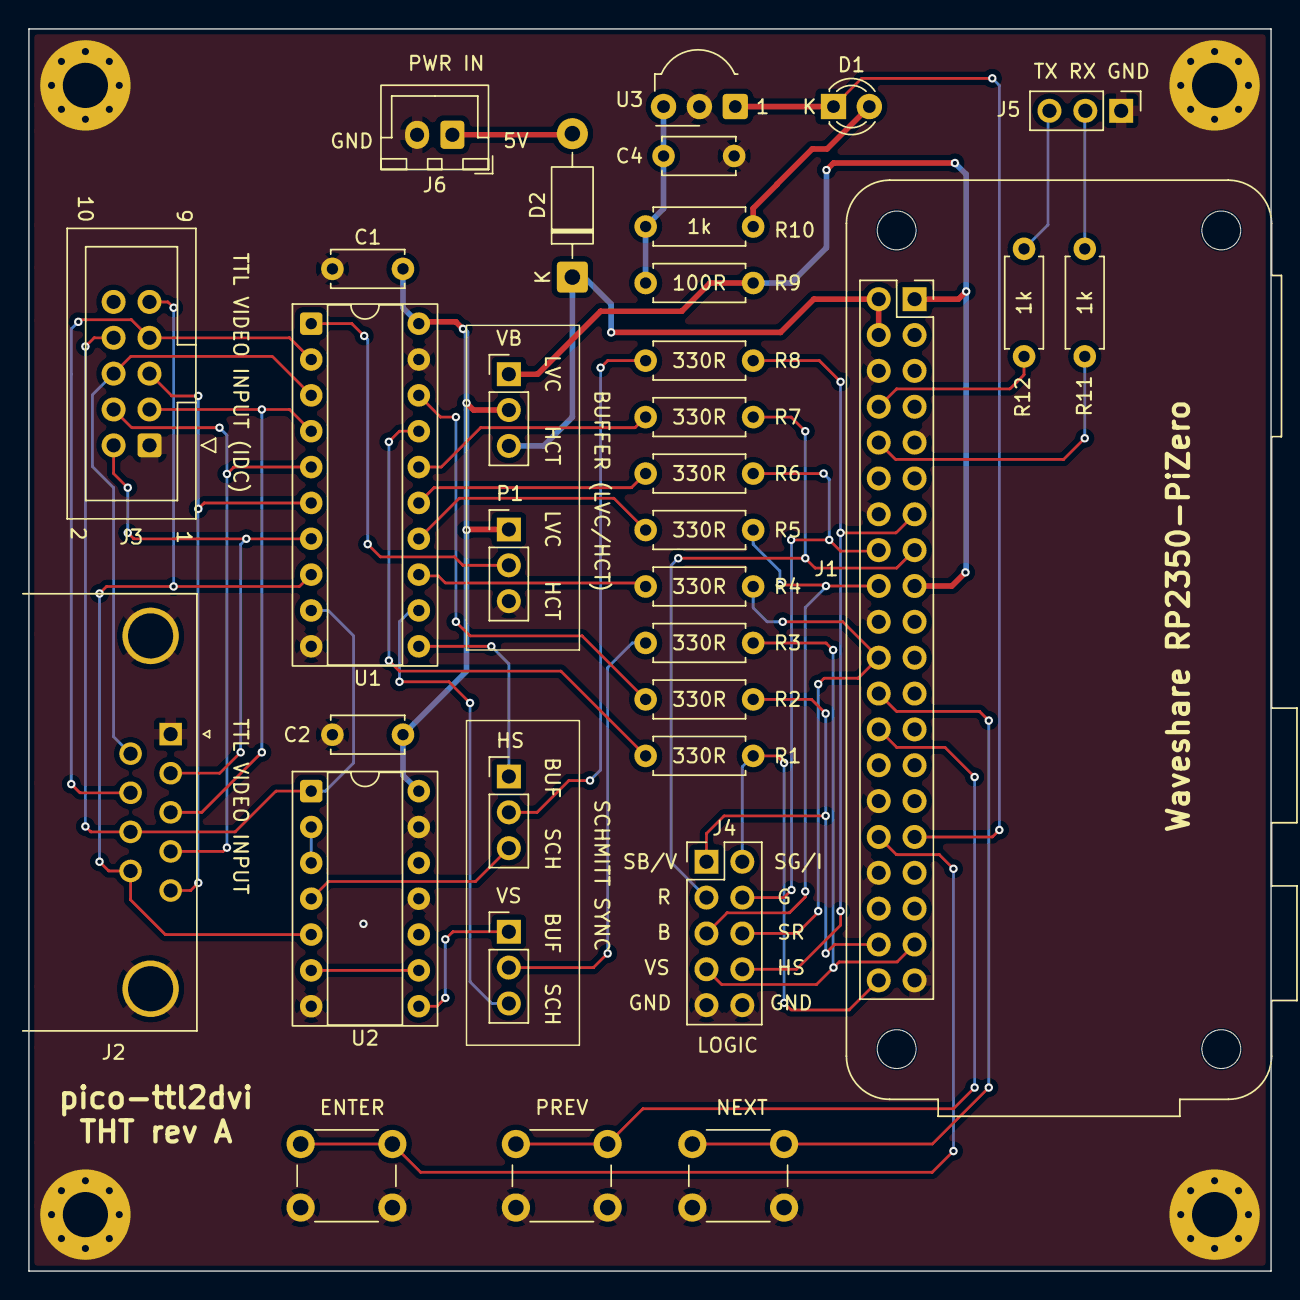
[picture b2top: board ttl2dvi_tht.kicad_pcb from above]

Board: 2 copper layers, 88.0 x 88.0 mm, 37 parts (0 on the bottom side), 46 nets.

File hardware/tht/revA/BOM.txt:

ttl2dvi THT adapter board - bill of materials (rev A)

Ref        Qty  Value / part                   Package                  Optional  Notes
---------  ---  -----------------------------  -----------------------  --------  ------------------------------------------
J1           1  2x20 female header             2.54 mm                  no        Waveshare RP2350-PiZero plugs in face down
-            1  Waveshare RP2350-PiZero        module                   no
J2           1  DE9 male, right angle          PCB mount                yes       video in; fit J2 or J3, use one input only
J3           1  2x5 IDC box header             2.54 mm                  yes       video in via DE9-to-IDC10 cable
U1           1  74LVC245A or 74HCT541          DIP-20                   no        set JP1/JP2 to match
-            1  IC socket                      DIP-20                   no
U2           1  74LVC14A or 74HCT14            DIP-14                   yes       Schmitt on the syncs; same family as U1
-            1  IC socket                      DIP-14                   yes       with U2
R1-R8        8  330R 1/4 W                     axial                    no
C1, C2       2  100nF ceramic                  disc, 5 mm               no        buffer supply decoupling
JP1-JP4      4  1x3 pin header                 2.54 mm                  no
-            4  jumper shunt                   2.54 mm                  no        one per JP1-JP4
SW1-SW3      3  tactile push button            6 mm                     yes       PREV / NEXT / ENTER menu buttons
U3           1  VS1838B/TSOP38238 IR receiver  3-pin                    yes       IR remote
R9           1  100R 1/4 W                     axial                    yes       U3 supply; required when U3 is fitted
C4           1  100nF ceramic                  disc, 5 mm               yes       at U3; required when U3 is fitted
D1           1  LED 3 mm                       THT                      yes       IR activity, debug only
R10          1  1k 1/4 W                       axial                    yes       with D1
J4           1  2x5 pin header                 2.54 mm                  yes       logic analyser
J5           1  1x3 pin header                 2.54 mm                  yes       UART console
R11, R12     2  1k 1/4 W                       axial                    yes       with J5; fit before J1 (under the module)
J6           1  JST XH 2-pin                   2.50 mm                  yes       external 5 V in
D2           1  1N5819 Schottky                DO-41                    yes       with J6
